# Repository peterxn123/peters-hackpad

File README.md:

# peters-hackpad

Physical build:

Hi! This is my hackpad created as part of Hack Club's hackpad YSWS program - hackpad.hackclub.com

To be honest, this was one of my first times using Fusion and my first ever time using KiCad! I wanted to make something with a clean slanted design for good ergonomic input, 6 keys, RGB neopixels for cool backlighting and a rotary encoder for volume control.

BOM:

- 1x Xiao RP2040
- 6x Cherry MX Key Switches
- 6x DSA Keycaps
- 4x M3x16 SHCS bolts
- 2x SK6812 mini LEDs
- 1x Case - 2 3D printed parts
- 1x custom PCB

Schematic:

PCB design:

Case:

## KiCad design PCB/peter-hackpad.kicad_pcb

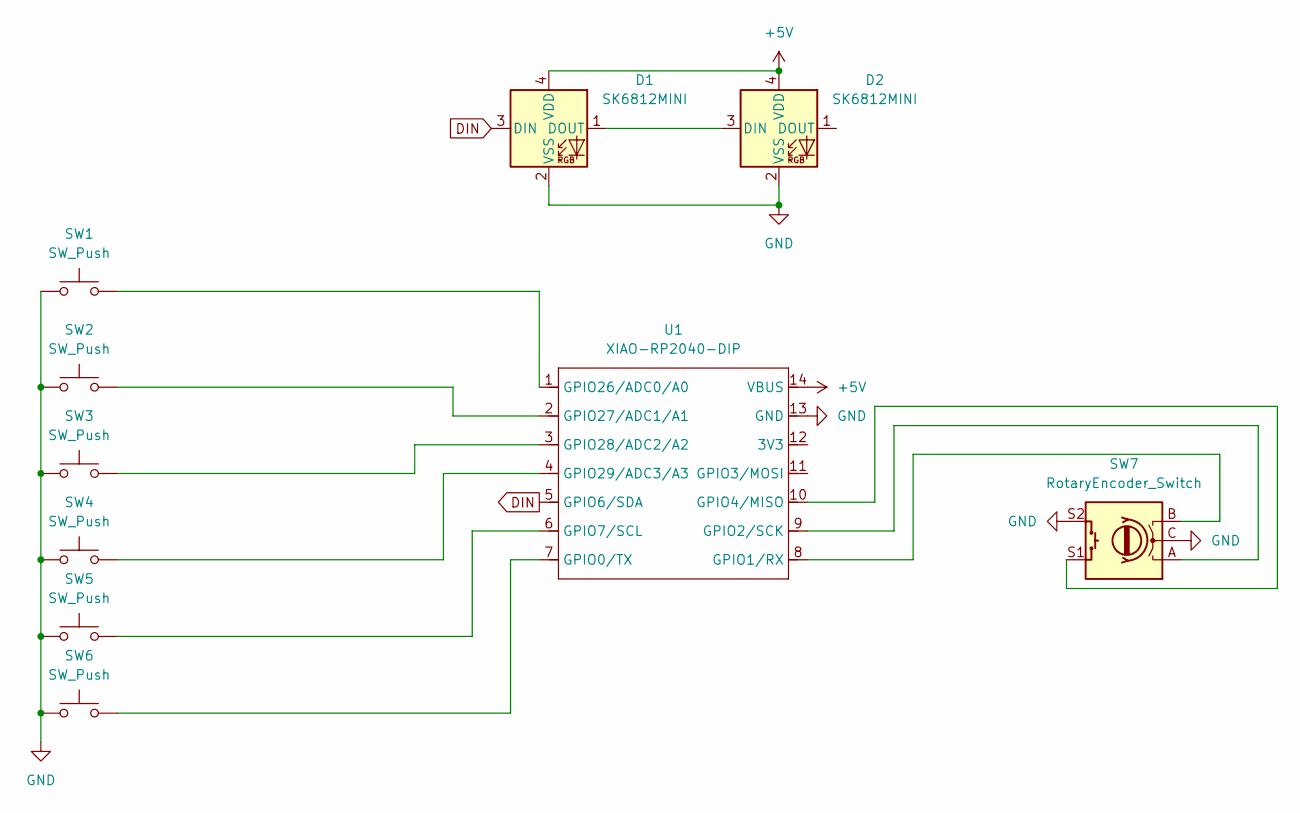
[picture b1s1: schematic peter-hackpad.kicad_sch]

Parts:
D1, D2: SK6812MINI; LED_SK6812MINI_PLCC4_3.5x3.5mm_P1.75mm
SW1, SW2, SW3, SW4, SW5, SW6: SW_Push; SW_Cherry_MX_1.00u_PCB
SW7: RotaryEncoder_Switch; RotaryEncoder_Alps_EC11E-Switch_Vertical_H20mm
U1: XIAO-RP2040-DIP

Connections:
+5V: D1.4 (VDD), D2.4 (VDD), U1.14 (VBUS)
DIN: D1.3 (DIN), U1.5 (GPIO6/SDA)
GND: D1.2 (VSS), D2.2 (VSS), SW1.1, SW2.1, SW3.1, SW4.1, SW5.1, SW6.1, SW7.C, SW7.S2, U1.13 (GND)
unnamed: D1.1 (DOUT), D2.3 (DIN)
unnamed: SW6.2, U1.7 (GPIO0/TX)
unnamed: SW7.B, U1.8 (GPIO1/RX)
unnamed: SW7.A, U1.9 (GPIO2/SCK)
unnamed: SW7.S1, U1.10 (GPIO4/MISO)
unnamed: SW5.2, U1.6 (GPIO7/SCL)
unnamed: SW1.2, U1.1 (GPIO26/ADC0/A0)
unnamed: SW2.2, U1.2 (GPIO27/ADC1/A1)
unnamed: SW3.2, U1.3 (GPIO28/ADC2/A2)
unnamed: SW4.2, U1.4 (GPIO29/ADC3/A3)

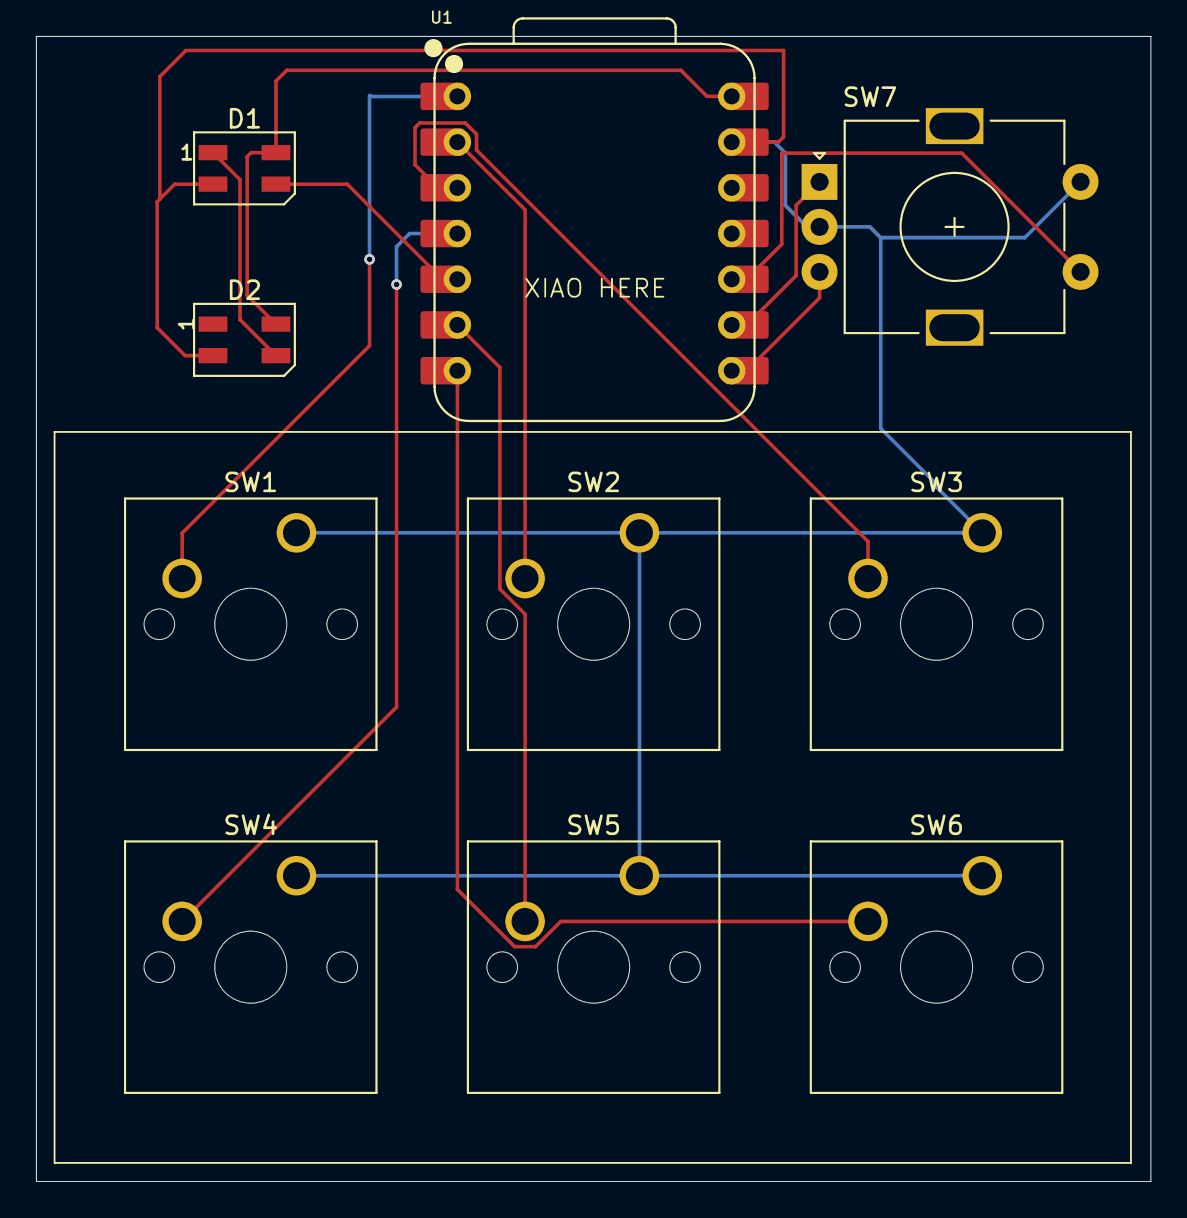
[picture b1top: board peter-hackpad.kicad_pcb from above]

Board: 2 copper layers, 61.9 x 63.6 mm, 10 parts (0 on the bottom side), 13 nets.

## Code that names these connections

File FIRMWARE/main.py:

import digitalio
import microcontroller
import board
import time


from kmk.kmk_keyboard import KMKKeyboard
from kmk.scanners.keypad import KeysScanner
from kmk.scanners.encoder import RotaryioEncoder
from kmk.extensions.rgb import RGB
from kmk.keys import KC
from kmk.modules.encoder import EncoderHandler

keyboard = KMKKeyboard()
keyboard.matrix = [
    KeysScanner(
        pins=[
            board.A0,                       # GPIO26
            board.A1,                       # GPIO27
            board.A2,                       # GPIO28
            board.A3,                       # GPIO29
            board.D7,                       # GPIO7
            microcontroller.pin.GPIO0,      # GPIO0
            microcontroller.pin.GPIO4       # Encoder button S1
        ],
        value_when_pressed=False,
        pull=True
    ),
    RotaryioEncoder(
        pin_a=microcontroller.pin.GPIO2,
        pin_b=microcontroller.pin.GPIO1
    )
]

keyboard.coord_mapping = [0, 1, 2, 3, 4, 5, 6]

rgb = RGB(
    pixel_pin=microcontroller.pin.GPIO6,
    num_pixels=2,
    rgb_order=(1, 0, 2),
    brightness_limit=255,
)
keyboard.extensions.append(rgb)

encoder_handler = EncoderHandler()
encoder_handler.encoder_map = [
    ((KC.VOLD, KC.VOLU),)
]
keyboard.modules.append(encoder_handler)

keyboard.keymap = [
    [
        KC.LGUI(KC.D),
        KC.LGUI(KC.TAB),
        KC.LGUI(KC.L),
        KC.LGUI(KC.E),
        KC.LCTL(KC.C),
        KC.LCTL(KC.V),
        KC.ENTER
    ]
]


@keyboard.on_startup
def set_initial_leds():
    base_color = (0, 0, 50)
    rgb.set_rgb_value(0, base_color)
    rgb.set_rgb_value(1, base_color)


@keyboard.on_key
def animate_on_key(key, pressed, **kwargs):
    if pressed:
        pulse_animation()


def pulse_animation():
    steps = 10
    for i in range(steps):
        val = int(255 * (i / steps))
        rgb.set_rgb_value(0, (val, val, val))
        rgb.set_rgb_value(1, (val, val, val))
        time.sleep(0.01)

    for i in range(steps):
        val = int(50 * (1 - i / steps))
        rgb.set_rgb_value(0, (0, 0, val))
        rgb.set_rgb_value(1, (0, 0, val))
        time.sleep(0.01)


if __name__ == '__main__':
    keyboard.go()

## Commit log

2025-05-31 Created the folders for the hackpad files. Added the step files for the hackpad case.
2025-06-01 Added all necessary project files in accordance with the guidance for how to structure your hackpad repository.
2025-06-01 Updated the top case to have a better design. Updated the CAD file with all designs together to match.
2025-06-01 Update README.md
    Updated README.md to add all details needed for the hackpad submission.
2025-06-01 Update README.md
    Added BOM
2025-06-01 Added missing PCB file
2025-06-01 Update main.py
    Updated key functions
2025-08-14 Update main.py to make it work
